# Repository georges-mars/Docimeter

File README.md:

Wearable Dosimeter

A wearable redesign of the OpenDosimeter platform focused on compact electronics, custom PCB integration, embedded firmware, and practical radiation-monitoring applications.

Overview

The Wearable OpenDosimeter is a redesigned and wearable implementation of the OpenDosimeter concept. The project takes the original open-source dosimeter architecture and re-engineers it around a compact, portable form factor intended to be worn by the user.

The redesign brings together:

Embedded systems and firmware development

Custom PCB design and redesign

Radiation sensing and measurement

Power management

Mechanical and enclosure design

Human-centered wearable integration

Hardware and software testing

The main objective was not simply to reproduce the original device, but to explore how its electronics and mechanical architecture could be adapted into a more compact and wearable platform.

Project Motivation

Traditional prototype radiation-monitoring systems can become inconvenient when the electronics, battery, sensor, and user interface are separated into a relatively large enclosure.

This project explores a different approach: integrating the sensing, processing, power, and user-interface subsystems into a compact wearable device.

The redesign therefore focuses on three major engineering challenges:

Electronics integration — fitting the required circuitry into a smaller custom PCB.

Wearability — designing the physical system around a form factor that can be comfortably carried or worn.

System integration — ensuring that sensing, processing, power, firmware, and mechanical components work together as one system.

Project Goals

The primary goals of the project are:

Redesign the original OpenDosimeter electronics for a wearable implementation.

Develop a compact custom PCB.

Integrate the radiation-sensing subsystem with the embedded controller.

Implement firmware for sensor acquisition and measurement processing.

Provide a practical user interface for viewing measurements.

Integrate rechargeable battery power and power management.

Develop a compact mechanical enclosure.

Create a modular hardware and firmware architecture that can be extended in future revisions.

Maintain clear documentation to support further development.

Key Features

Wearable form factor

Custom PCB

Embedded microcontroller

Radiation sensing

Real-time measurement processing

On-device display/interface

Rechargeable battery operation

Integrated power management

Compact electronics and mechanical integration

Modular firmware architecture

Expandable data logging and communication architecture

System Architecture

The system is organized into several functional layers: sensing, processing, user interface, data handling, and power management.

flowchart TB
    subgraph SENSING["Sensing Layer"]
        RAD["Radiation Sensor"]
    end

    subgraph PROCESSING["Processing Layer"]
        MCU["Microcontroller"]
        DSP["Signal Processing<br/>Measurement Calculation"]
    end

    subgraph INTERFACE["User Interface"]
        DISP["Display"]
        ALERT["Alerts / Indicators"]
    end

    subgraph DATA["Data & Connectivity"]
        LOG["Data Logging"]
        COMM["Communication Interface"]
    end

    subgraph POWER["Power System"]
        BAT["Rechargeable Battery"]
        PMIC["Power Management"]
    end

    RAD --> MCU
    MCU --> DSP

    DSP --> DISP
    DSP --> ALERT
    DSP --> LOG
    MCU --> COMM

    BAT --> PMIC
    PMIC --> MCU
    PMIC --> RAD
    PMIC --> DISP

The architecture separates the device into logical subsystems so that individual components can be modified without requiring a complete redesign of the system.

Hardware Architecture

The hardware can be viewed as five major sections:

1. Radiation Detection

The radiation sensor detects ionizing radiation and produces an electrical signal that can be captured and processed by the microcontroller.

The sensing subsystem is one of the most important parts of the device because measurement quality depends on the sensor, signal conditioning, acquisition method, calibration, and physical configuration.

2. Processing

The microcontroller serves as the central processing unit.

It handles:

Sensor acquisition

Signal processing

Measurement calculations

Display updates

System control

Power-management logic

Communication with external systems

3. User Interface

The user interface provides a convenient way to observe radiation measurements and system status directly from the wearable device.

Depending on the hardware revision, this can include:

Display output

Status indicators

Audible or visual alerts

User input controls

4. Data and Communication

The architecture can support data logging and communication interfaces for future expansion.

Potential interfaces include:

Serial communication

USB

Bluetooth

Wi-Fi

External data logging

5. Power Management

The wearable is designed around rechargeable battery operation.

The power subsystem is responsible for:

Battery input

Voltage regulation

Power distribution

Charging

Protection

Power-state management

Firmware Architecture

The firmware follows a continuous measurement-and-processing cycle.

flowchart TD
    A["System Startup"] --> B["Initialize Hardware"]
    B --> C["Initialize Radiation Sensor"]
    C --> D["Initialize Display & Peripherals"]
    D --> E["Begin Measurement"]

    E --> F["Acquire Sensor Data"]
    F --> G["Process & Validate Data"]
    G --> H["Calculate Radiation Measurements"]

    H --> I["Update Display"]
    H --> J["Store Measurement Data"]
    H --> K["Generate Alerts"]

    I --> L{"Continue Monitoring?"}
    J --> L
    K --> L

    L -->|"Yes"| F
    L -->|"No"| M["Safe Shutdown"]

The firmware is designed around a repeated acquisition and processing loop. This allows the device to continuously monitor the radiation sensor while updating the user interface and other system functions.

Measurement Pipeline

The general measurement pipeline is:

flowchart LR
    A["Radiation Event"] --> B["Radiation Sensor"]
    B --> C["Electrical Signal"]
    C --> D["Microcontroller"]
    D --> E["Signal Processing"]
    E --> F["Measurement Calculation"]
    F --> G["User Interface"]
    F --> H["Data Storage"]
    F --> I["Alert System"]

This separation makes it possible to improve the signal-processing or measurement algorithms without fundamentally changing the mechanical enclosure.

PCB Redesign

A major part of the project is the redesign of the electronics around a wearable form factor.

The PCB redesign considers:

Component placement

PCB dimensions

Sensor connections

Power distribution

Grounding

Signal routing

Connector placement

Programming/debugging access

Battery connections

Mechanical mounting

Enclosure constraints

Manufacturability

The PCB and mechanical enclosure are treated as a combined system rather than as independent designs.

PCB Design Priorities

The redesign prioritizes:

Compactness

Reducing unnecessary board area to make the final device easier to wear.

Serviceability

Maintaining reasonable access to programming, debugging, charging, and important electrical connections.

Signal Integrity

Keeping sensitive measurement and digital circuitry appropriately routed and powered.

Mechanical Integration

Positioning connectors, displays, sensors, and mounting points according to the enclosure geometry.

Mechanical & Wearable Design

The mechanical redesign converts the electronics from a general-purpose prototype into a wearable platform.

The enclosure is designed around:

PCB dimensions

Battery dimensions

Sensor location

Display visibility

Connector access

User interaction

Mechanical protection

Wearability

The mechanical system should also provide sufficient protection for the electronics while avoiding unnecessary bulk.

flowchart TB
    A["Wearable Enclosure"] --> B["Custom PCB"]
    A --> C["Rechargeable Battery"]
    A --> D["Radiation Sensor"]
    A --> E["Display / User Interface"]
    A --> F["Charging & I/O Access"]

    B --> G["Electrical Integration"]
    C --> G
    D --> G
    E --> G
    F --> G

Engineering Workflow

The project follows an iterative engineering workflow:

flowchart LR
    A["Requirements"] --> B["System Architecture"]
    B --> C["Circuit & PCB Design"]
    C --> D["Mechanical Design"]
    D --> E["Prototype"]
    E --> F["Firmware Integration"]
    F --> G["Testing"]
    G --> H["Validation"]
    H --> I{"Issues Found?"}
    I -->|"Yes"| C
    I -->|"No"| J["Revision / Final Prototype"]

This iterative approach allows electrical, firmware, and mechanical problems to be identified early and incorporated into subsequent revisions.

Development Tools

The project can be developed using a combination of hardware, firmware, CAD, and documentation tools.

Area

Tools / Technologies

PCB Design

KiCad

Firmware

C / C++

Embedded Development

PlatformIO / Arduino-compatible workflow

Data Processing

Python

Mechanical Design

CAD software

Version Control

Git / GitHub

Documentation

Markdown

Prototyping

PCB fabrication, 3D printing and laboratory equipment

The exact tools may vary between hardware revisions.

Suggested Repository Structure

Wearable-OpenDosimeter/
│
├── firmware/
│   ├── src/
│   ├── include/
│   ├── lib/
│   └── platformio.ini
│
├── hardware/
│   ├── schematic/
│   ├── pcb/
│   ├── gerbers/
│   └── bom/
│
├── mechanical/
│   ├── cad/
│   ├── enclosure/
│   └── drawings/
│
├── documentation/
│   ├── design/
│   ├── testing/
│   └── calibration/
│
├── images/
│   ├── pcb/
│   ├── enclosure/
│   └── prototype/
│
├── tests/
│
├── LICENSE
└── README.md

Testing & Validation

Testing should be performed progressively rather than attempting to validate the complete device at once.

Electrical Testing

Verify:

Supply voltages

Current consumption

Battery operation

Charging behavior

Regulator outputs

GPIO functionality

Communication interfaces

PCB connectivity

Firmware Testing

Verify:

Sensor initialization

Sensor data acquisition

Measurement calculations

Display operation

Error handling

Communication

Power-management behavior

Mechanical Testing

Verify:

PCB fit

Battery fit

Connector accessibility

Sensor placement

Enclosure assembly

Wearability

Mechanical robustness

Measurement Validation

Radiation measurements should be evaluated using appropriate calibration and validation procedures.

Important factors include:

Sensor response

Radiation source characteristics

Radiation energy

Measurement geometry

Environmental conditions

Sensor-to-source distance

Electronics response

Statistical variation

Calibration

Accurate radiation measurement requires appropriate calibration.

A calibration procedure should establish the relationship between the sensor's electrical response and the radiation quantity being reported.

Depending on the measurement architecture, calibration may involve:

Establishing a controlled measurement setup.

Recording sensor output under known conditions.

Repeating measurements to evaluate variability.

Developing the required conversion relationship.

Validating the resulting measurements against an appropriate reference.

Documenting calibration conditions and limitations.

Calibration results should be stored alongside the relevant firmware and hardware revision where possible.

Safety & Measurement Disclaimer

This project is intended primarily for educational, research, and prototyping purposes.

A prototype radiation detector should not automatically be considered a certified radiation-protection instrument.

For applications involving occupational exposure, medical use, regulatory compliance, or other safety-critical decisions, the device would require appropriate calibration, validation, certification, and compliance with applicable standards and regulations.

Design Philosophy

The project is guided by several engineering principles:

Modularity

Hardware, firmware, and mechanical components should remain modular so that future revisions can replace individual subsystems without redesigning the entire platform.

Iterative Development

The device is developed through repeated cycles of design, fabrication, testing, measurement, and improvement.

Human-Centered Engineering

The redesign considers how the device will actually be worn, interacted with, maintained, and used rather than optimizing only for laboratory functionality.

Open Development

Where permitted by the original project license, design files and documentation should remain accessible so that other developers and researchers can study and improve the platform.

Future Improvements

Potential future development areas include:

Improved radiation sensor integration

Improved calibration procedures

Smaller PCB revisions

Lower-power operation

Extended battery life

Wireless data transmission

Mobile application integration

Cloud-based measurement logging

GPS-based radiation mapping

Improved enclosure ergonomics

Haptic, audible, or visual alerts

More advanced measurement algorithms

Automated test procedures

Improved manufacturing documentation

Project Status

Status: Prototype / Research & Development

The current project represents a redesign of the OpenDosimeter concept into a wearable platform. The hardware, firmware, PCB, mechanical enclosure, and measurement system can continue to evolve through additional testing and design iterations.

Contribution

The project involves work across multiple engineering disciplines, including:

Embedded systems

Firmware development

PCB design and redesign

Electrical hardware integration

Mechanical integration

Wearable product design

System testing

Technical documentation

The redesign focuses particularly on integrating these disciplines into a single compact device.

Acknowledgements

This project is based on the concept and work of the OpenDosimeter open-source project.

The original project's contributors and open-source community are acknowledged for providing the foundation on which this wearable redesign is being explored.

Where original OpenDosimeter hardware, firmware, documentation, or design elements are retained, the applicable original licensing and attribution requirements should be preserved.

Author

George Wambugu Mwangi

BSc Mechatronics Engineering
Dedan Kimathi University of Technology (DeKUT), Kenya

Areas of Contribution

Embedded Systems

Firmware Development

PCB Redesign

Hardware Integration

Mechanical Integration

Wearable Device Development

System Testing

Technical Documentation

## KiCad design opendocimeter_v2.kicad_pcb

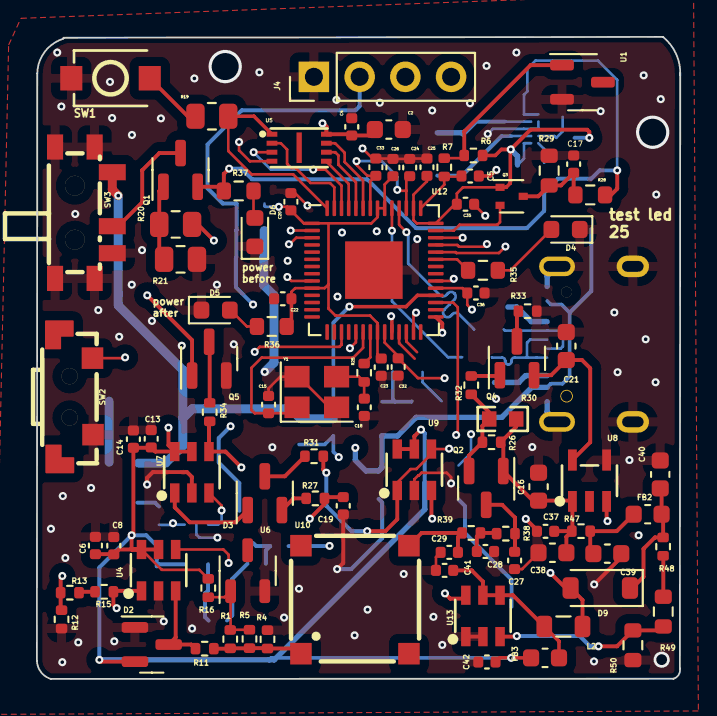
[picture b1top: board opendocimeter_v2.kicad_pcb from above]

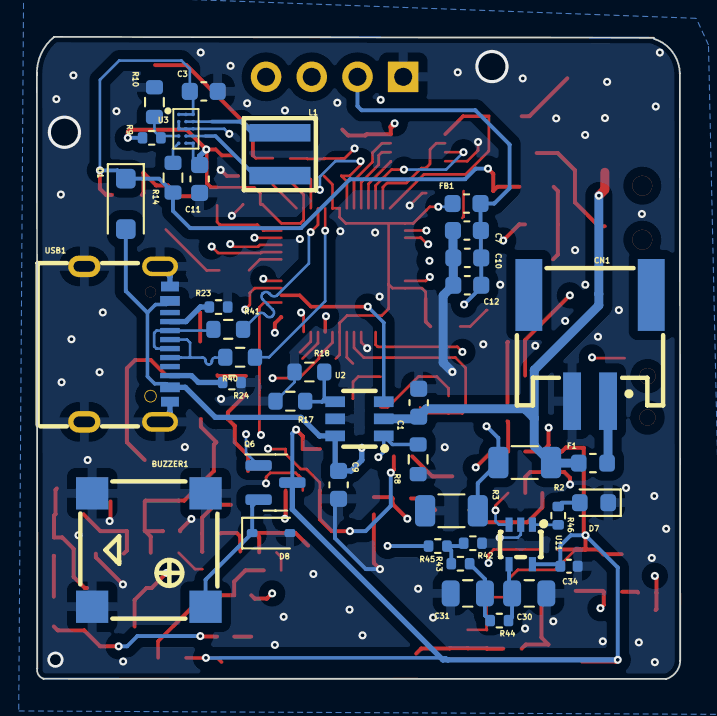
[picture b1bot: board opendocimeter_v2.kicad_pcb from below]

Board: 4 copper layers, 35.7 x 35.7 mm, 133 parts (40 on the bottom side), 80 nets.

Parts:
BUZZER1: SMD-7525-3627-16Ω; BUZ-SMD_4P-L7.5-W7.5-BR
C1, C7, C9, C10: 10u; C_0603_1608Metric
C2, C16, C21: 2.2u; C_0603_1608Metric
C3, C11: 22u; C_0603_1608Metric
C4, C6, C13, C20, C22, C23, C24, C25, C26, C27, C28, C29, C33, C34, C35, C37: 100n; C_0402_1005Metric
C5, C32, C36: 2.2u; C_0402_1005Metric
C8, C14, C41, C42: 10u; C_0402_1005Metric
C12: 100n; C_0603_1608Metric
C15, C18: 10p; C_0402_1005Metric
C17: 1n; C_0402_1005Metric
C19: 470p; C_0402_1005Metric
C30, C31: 47u; C_0805_2012Metric
C38, C39, C40: 4.7u; C_0603_1608Metric
CN1: HC-PH-2AWT; CONN-SMD_PH-2AWT
D1: MBR1020VL; D_SOD-123F
D2, D3: BAT54S; SOT-23
D4, D5, D6, D7: LED; LED_0603_1608Metric
D8: PMEG4010BEA,115; D_SOD-323
D9: PMEG4010CEH; D_SOD-123
F1: 06D0750D; Fuse_0603_1608Metric
FB1, FB2, FB3: 1k; C_0603_1608Metric
J4: Conn_01x04_Pin; PinHeader_1x04_P2.54mm_Vertical
L1: XFL4015-471MEC; IND-SMD_L4.0-W4.0_XGL4020
L2: 47u; L_0805_2012Metric
Q1: DMG2305UX-13; SOT-23
Q2, Q4: MMBT5088LT1G; SOT-23
Q3: DMG1012T; SOT-523
Q5, Q6: 2N7002; SOT-23
R1, R5, R48: 210k; R_0402_1005Metric
R2, R3: 499k; R_1206_3216Metric
R4, R12, R13, R15, R16, R25, R34, R42, R43, R44, R46: 1k; R_0402_1005Metric
R6: 200; R_0402_1005Metric
R7: 1; R_0402_1005Metric
R8, R50: 10k; R_0603_1608Metric
R9: 511k; R_0402_1005Metric
R10: 91k; R_0603_1608Metric
R11, R27, R47: 100; R_0402_1005Metric
R14, R29: 100k; R_0603_1608Metric
R17, R18: 1.8k; R_0603_1608Metric
R19, R20: 1k; R_0805_2012Metric
R21: 47k; R_0805_2012Metric
R23, R24: 5.1k; R_0402_1005Metric
R26: 24k; R_0402_1005Metric
R28: 200k; R_0603_1608Metric
R30: NTCS0603E3103FLT; R0603
R31: 10k; R_0402_1005Metric
R32, R33: 49.9k; R_0402_1005Metric
R35, R36, R37: 2K; R_0603_1608Metric
R38, R39: 49.9; R_0402_1005Metric
R40, R41: 27; R_0603_1608Metric
R45: 5.6k; R_0402_1005Metric
R49: 22k; R_0603_1608Metric
SW1: SW_Push; SW-SMD_L3.9-W3.0-P4.45
SW2: SW_Push; SW-SMD_SHOU_TS36CA-0.6
SW3: SK-3296S-01-L3; SW-SMD_SK-3296S-01-L3
U1, U6: LM4040AIM3-3.0+T; SOT-23-3
U2: BQ21040DBVR; SOT-23-6_L2.9-W1.6-P0.95-LS2.8-BR
U3: TPS63805YFFR; DSBGA-15_L2.3-W1.3-R5-C3-P0.40-TL
U4, U7, U9: OPA357AIDBVR; SOT-23-6_L2.9-W1.6-P0.95-LS2.8-BL
U5: W25Q16JVUXIQ; USON-8_L3.0-W2.0-P0.50-BL-EP
U8: TPS7B6950DBVR; SOT-23-5_L3.0-W1.7-P0.95-LS2.8-BL
U10: MICROFC-60035-SMT-TR1; OPTO-SMD_MICROFC-60035-SM
U11: TLV3201AIDCKR; SC-70-5_L2.1-W1.3-P0.65-LS2.1-TL
U12: RP2040; QFN-56-1EP_7x7mm_P0.4mm_EP3.2x3.2mm
U13: MAX5026EUT+T; SOT-23-6_L2.9-W1.6-P0.95-LS2.8-BL
USB1: TYPE-C 16PIN 2MD(073); USB-C-SMD_TYPE-C-6PIN-2MD-073
Y1: XL2EL89CMI-111YLC-12M; Crystal_SMD_3225-4Pin_3.2x2.5mm

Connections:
25: R35.2, U12.37 (GPIO25)
29: Q3.2 (S), U12.41 (GPIO29_ADC3)
/d+: R40.2, U12.47 (USB_DP)
/d-: R41.2, U12.46 (USB_DM)
ADC_AVDD: C5.1, R7.2, U12.43 (ADC_AVDD)
BF: C27.2, Q2.3 (E), R38.1
BTN: SW2.2, U12.17 (GPIO14)
CATHODE: C29.1, R39.2, U10.3 (Cathode)
CHG: U2.3 (~CHG), U12.32 (GPIO21)
D+: R40.1, USB1.6 (DP1), USB1.8 (DP2)
D-: R41.1, USB1.5 (DN2), USB1.7 (DN1)
DVDD: C24.2, C32.1, C33.2, U12.23 (DVDD), U12.45 (VREG_VOUT), U12.50 (DVDD)
FB: R9.2, R10.1, U3.D1 (FB)
GND: BUZZER1.2, BUZZER1.3, BUZZER1.4, C1.2, C2.2, C3.2, C4.2, C5.2, C6.2, C7.2, C8.2, C9.2, C10.2, C11.2, C12.2, C13.2, C14.2, C15.2, C16.2, C17.2, C18.2, C19.2, C20.2, C21.2, C22.2, C23.2, C24.1, C25.2, C26.2, C27.1, C28.1, C29.2, C30.2, C31.1, C32.2, C33.1, C34.1, C35.1, C36.2, C37.2, C38.2, C39.2, C40.1, C41.2, C42.2, CN1.2, D2.1 (A), D4.1 (K), D5.1 (K), D6.1 (K), D7.1 (K), D8.2 (A), J4.1, Q5.2 (S), R3.2, R4.1, R8.1, R10.2, R12.2, R17.2, R18.2, R21.2, R23.2, R24.2, R29.1, R33.2, R42.2, R50.2, SW1.1, SW2.1, SW3.3, SW3.4 (EH), U1.2 (Negative), U2.5 (GND), U3.B1 (MODE), U3.C1 (AGND), U3.C2 (GND), U3.C3 (GND), U4.2 (V-), U5.4 (GND), U6.2 (Negative), U7.2 (V-), U8.3 (GND), U8.4 (GND), U9.2 (V-), U11.2 (GND), U12.19 (TESTEN), U12.57 (GND), U13.1 (PGND), U13.2 (GND), USB1.1 (GND), USB1.12 (GND), USB1.13 (SHELL), USB1.14 (SHELL), Y1.2, Y1.4
IN-: C19.1, R27.2, R34.2, U7.4 (IN-), U9.3 (IN+)
INT: R46.2, U11.1 (OUT), U12.27 (GPIO16)
IOVDD: C2.1, C4.1, C11.1, C20.1, C22.1, C23.1, C25.1, C26.1, C35.2, C36.1, FB1.1, Q3.1 (G), R6.1, R9.1, R36.2, U3.E2 (VOUT), U3.E3 (VOUT), U5.8 (VCC), U12.1 (IOVDD), U12.10 (IOVDD), U12.22 (IOVDD), U12.33 (IOVDD), U12.42 (IOVDD), U12.44 (VREG_IN), U12.48 (USB_VDD), U12.49 (IOVDD)
L1: L1.1, U3.B2 (L1), U3.B3 (L1)
L2: L1.2, U3.D2 (L2), U3.D3 (L2)
unnamed: C28.2, R38.2, R39.1
unnamed: C31.2, R43.1, R44.2
unnamed: C39.1, FB2.1, R47.2
unnamed: CN1.1, F1.2
unnamed: D2.3 (COM), R11.2, U4.3 (IN+)
unnamed: D3.1 (A), U7.1 (OUT)
unnamed: D3.3 (COM), R31.1
unnamed: D3.2 (K), R27.1
unnamed: D4.2 (A), R35.1
unnamed: D5.2 (A), R36.1
unnamed: D6.2 (A), R37.1
unnamed: D7.2 (A), R46.1
unnamed: BUZZER1.1, D8.1 (K), Q6.2 (S)
unnamed: D9.2 (A), L2.1, U13.6 (LX)
unnamed: C40.2, D9.1 (K), FB2.2, R48.1
unnamed: Q1.3 (D), SW3.2
unnamed: Q1.1 (G), R20.2, R21.1
unnamed: Q2.2 (B), R26.2, R30.2, R32.1
unnamed: C17.1, Q3.3 (D), R28.2, R29.2
unnamed: Q4.1 (C), R32.2
unnamed: Q4.3 (E), R33.1
unnamed: Q5.3 (D), R34.1
unnamed: R13.1, R15.2
unnamed: R19.1, SW1.2
unnamed: R42.1, R43.2, R45.1
unnamed: R48.2, R49.2
unnamed: R17.1, R18.1, U2.4 (ISET)
unnamed: R12.1, R13.2, U4.4 (IN-)
unnamed: R49.1, R50.1, U13.3 (FB)
unnamed: C41.1, FB3.1, L2.2, U13.4 (~SHDN), U13.5 (VCC)
unnamed: R23.1, USB1.4 (CC1)
unnamed: R24.1, USB1.10 (CC2)
OUT: C21.1, Q4.2 (B), U8.5 (OUT)
PEAK: R31.2, U9.1 (OUT), U9.4 (IN-), U12.39 (GPIO27_ADC1)
PG: R14.1, U3.E1 (PG)
PSU: C16.1, C37.1, C38.1, Q2.1 (C), R26.1, R30.1, R47.1, U8.1 (IN)
PWM: R45.2, U12.29 (GPIO18)
QSPI_SCLK: U5.6 (CLK), U12.52 (QSPI_SCLK)
QSPI_SD0: U5.5 (DI(IO0)), U12.53 (QSPI_SD0)
QSPI_SD1: U5.2 (DO(IO1)), U12.55 (QSPI_SD1)
QSPI_SD2: U5.3 (WP#(IO2)), U12.54 (QSPI_SD2)
QSPI_SD3: U5.7 (HOLD#orRESET#(IO3)), U12.51 (QSPI_SD3)
QSPI_SS: R19.2, U5.1 (~CS), U12.56 (QSPI_SS)
RST: Q5.1 (G), U12.34 (GPIO22)
SCL: J4.3, U12.3 (GPIO1)
SDA: J4.4, U12.2 (GPIO0)
SIG: R15.1, U4.1 (OUT), U7.3 (IN+), U11.3 (+IN), U12.38 (GPIO26_ADC0)
SIPM: R1.2, R4.2, R5.2, R11.1, U10.1 (Anode)
TCKR: Q6.1 (G), U12.9 (GPIO7)
TH: C30.1, R44.1, U11.4 (-IN)
TS: R8.2, U2.1 (TS), U12.31 (GPIO20)
VAA: C1.1, F1.1, R2.1, SW3.1, U2.2 (OUT)
VBAT: R2.2, R3.1, U12.40 (GPIO28_ADC2)
VBUS: C9.1, D1.2 (A), R20.1, U2.6 (VIN), USB1.2 (VBUS), USB1.11 (VBUS)
VCC: C6.1, C7.1, C8.1, C10.1, C12.1, C13.1, C14.1, C34.2, C42.1, D2.2 (K), FB1.2, FB3.2, J4.2, Q6.3 (D), R16.2, U4.5 (ENABLE), U4.6 (V+), U7.5 (ENABLE), U7.6 (V+), U9.5 (ENABLE), U9.6 (V+), U11.5 (VCC)
VDD: C3.1, D1.1 (K), Q1.2 (S), R14.2, R28.1, R37.2, U3.A1 (EN), U3.A2 (VIN), U3.A3 (VIN)
VREF: R6.2, R7.1, U1.1 (Positive)
VREF1: R1.1, R5.1, R16.1, U6.1 (Positive)
XIN: C15.1, U12.20 (XIN), Y1.1
XOUT: R25.2, U12.21 (XOUT)
XR: C18.1, R25.1, Y1.3
